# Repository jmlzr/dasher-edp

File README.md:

# Dasher eDP Mod

A mod that adds eDP to the X230. Soldered to the mainboard it turns the second DisplayPort of the docking port into an eDP port.

Unlike other mods this one is entirely passive (it's just a PCB with 2 connectors, nothing else) and was designed to be used with [Coreboot](https://www.coreboot.org/). That enables it to provide the best possible user experience, including:

* Working brightness control via ACPI
* Display works in firmware, at full resolution
* No extra power draw, the panel is only powered when needed

You can find the schematic as PDF in [doc/schematic.pdf](doc/schematic.pdf).

## License

Copyright (c) 2020-2026 Jens Mölzer.

This project is licensed under the CERN Open Hardware Licence Version 2 – Permissive (CERN-OHL-P-2.0), see [LICENSE](LICENSE).

**Exception:** The files in `dasher-edp.3d/` and `datasheets/` are **not** my work and are therefore **not** covered by this license.

## Similar Works

* [nitrocaster FHD mod](https://web.archive.org/web/20260723215018/https://nitrocaster.me/store/x220-x230-fhd-mod-kit.html): Demonstrated feasibility and inspired this work. Uses a microcontroller.
* Various others (see e.g. [here](https://github.com/lethedata/x220_x230-Mod_Kits) for a list) that all use active components and ugly hacks for brightness control.

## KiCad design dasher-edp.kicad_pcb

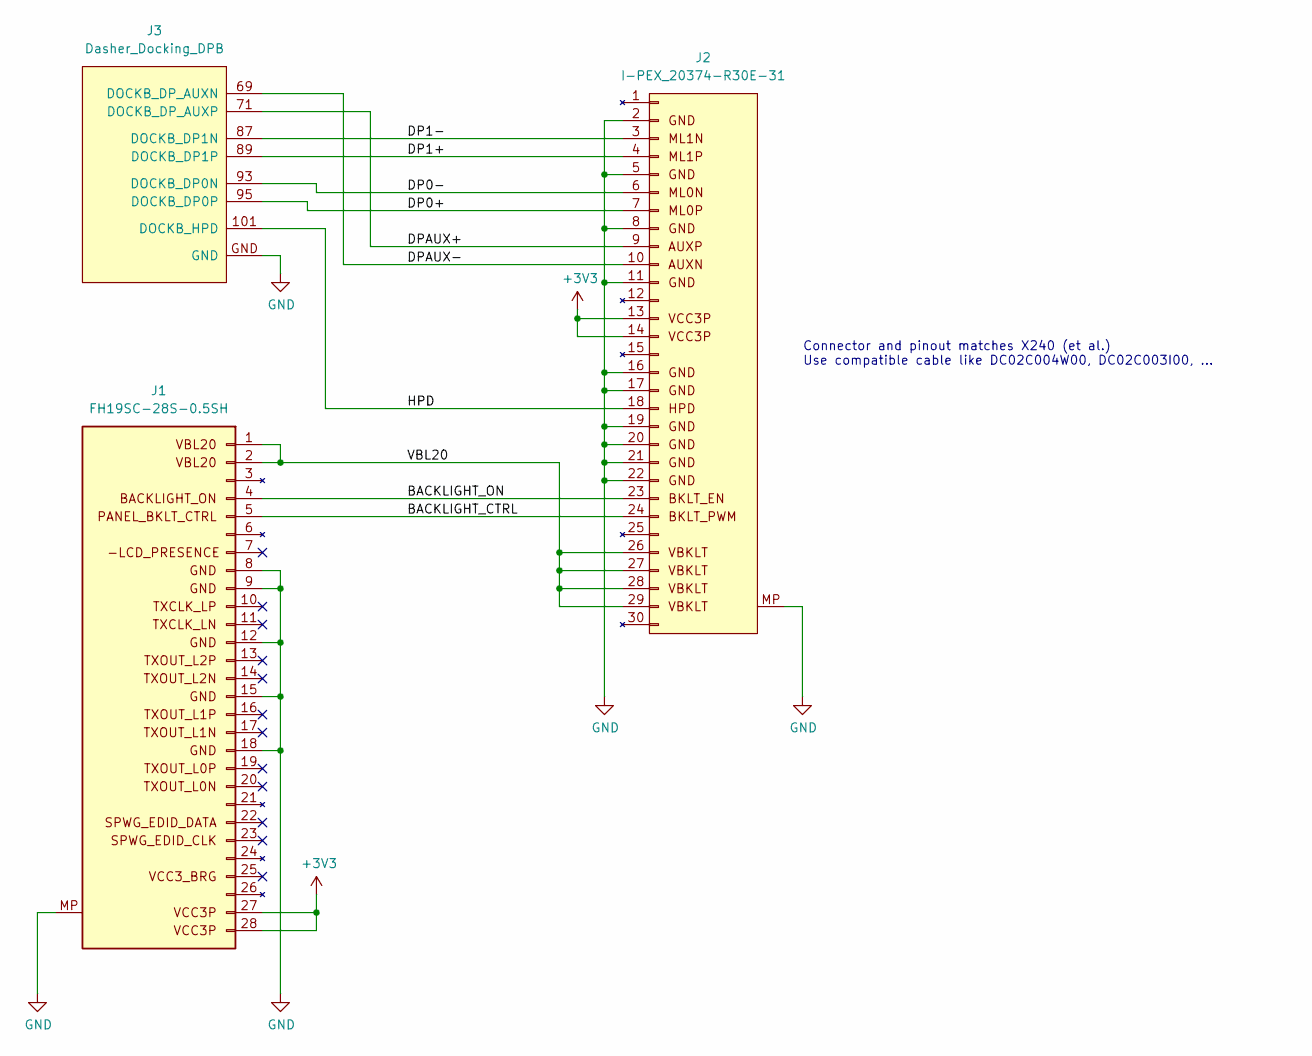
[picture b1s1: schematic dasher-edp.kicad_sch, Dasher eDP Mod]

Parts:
J1: FH19SC-28S-0.5SH
J2: I-PEX_20374-R30E-31
J3: Dasher_Docking_DPB; dasher_dock_dpb

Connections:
+3V3: J1.27, J1.28, J2.13, J2.14
/DP0+: J2.7, J3.95 (DOCKB_DP0P)
/DP0-: J2.6, J3.93 (DOCKB_DP0N)
/DP1+: J2.4, J3.89 (DOCKB_DP1P)
/DP1-: J2.3, J3.87 (DOCKB_DP1N)
/DPAUX+: J2.9, J3.71 (DOCKB_DP_AUXP)
/DPAUX-: J2.10, J3.69 (DOCKB_DP_AUXN)
GND: J1.8, J1.9, J1.12, J1.15, J1.18, J1.MP (MountPin), J2.2, J2.5, J2.8, J2.11, J2.16, J2.17, J2.19, J2.20, J2.21, J2.22, J2.MP (MountPin), J3.GND
unnamed: J1.1, J1.2, J2.26, J2.27, J2.28, J2.29
unnamed: J1.4, J2.23
unnamed: J1.5, J2.24
unnamed: J2.18, J3.101 (DOCKB_HPD)

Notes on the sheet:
Connector and pinout matches X240 (et al.) Use compatible cable like DC02C004W00, DC02C003I00, ...

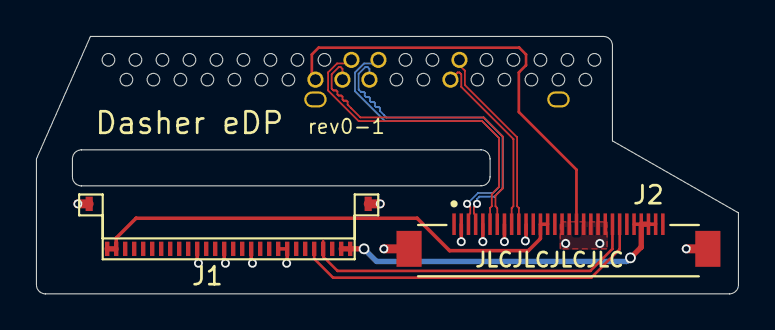
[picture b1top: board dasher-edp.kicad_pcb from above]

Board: 4 copper layers, 39.0 x 14.3 mm, 3 parts (0 on the bottom side), 12 nets.

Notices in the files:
dasher-edp.kicad_pcb:
License: CERN-OHL-P-2.0
